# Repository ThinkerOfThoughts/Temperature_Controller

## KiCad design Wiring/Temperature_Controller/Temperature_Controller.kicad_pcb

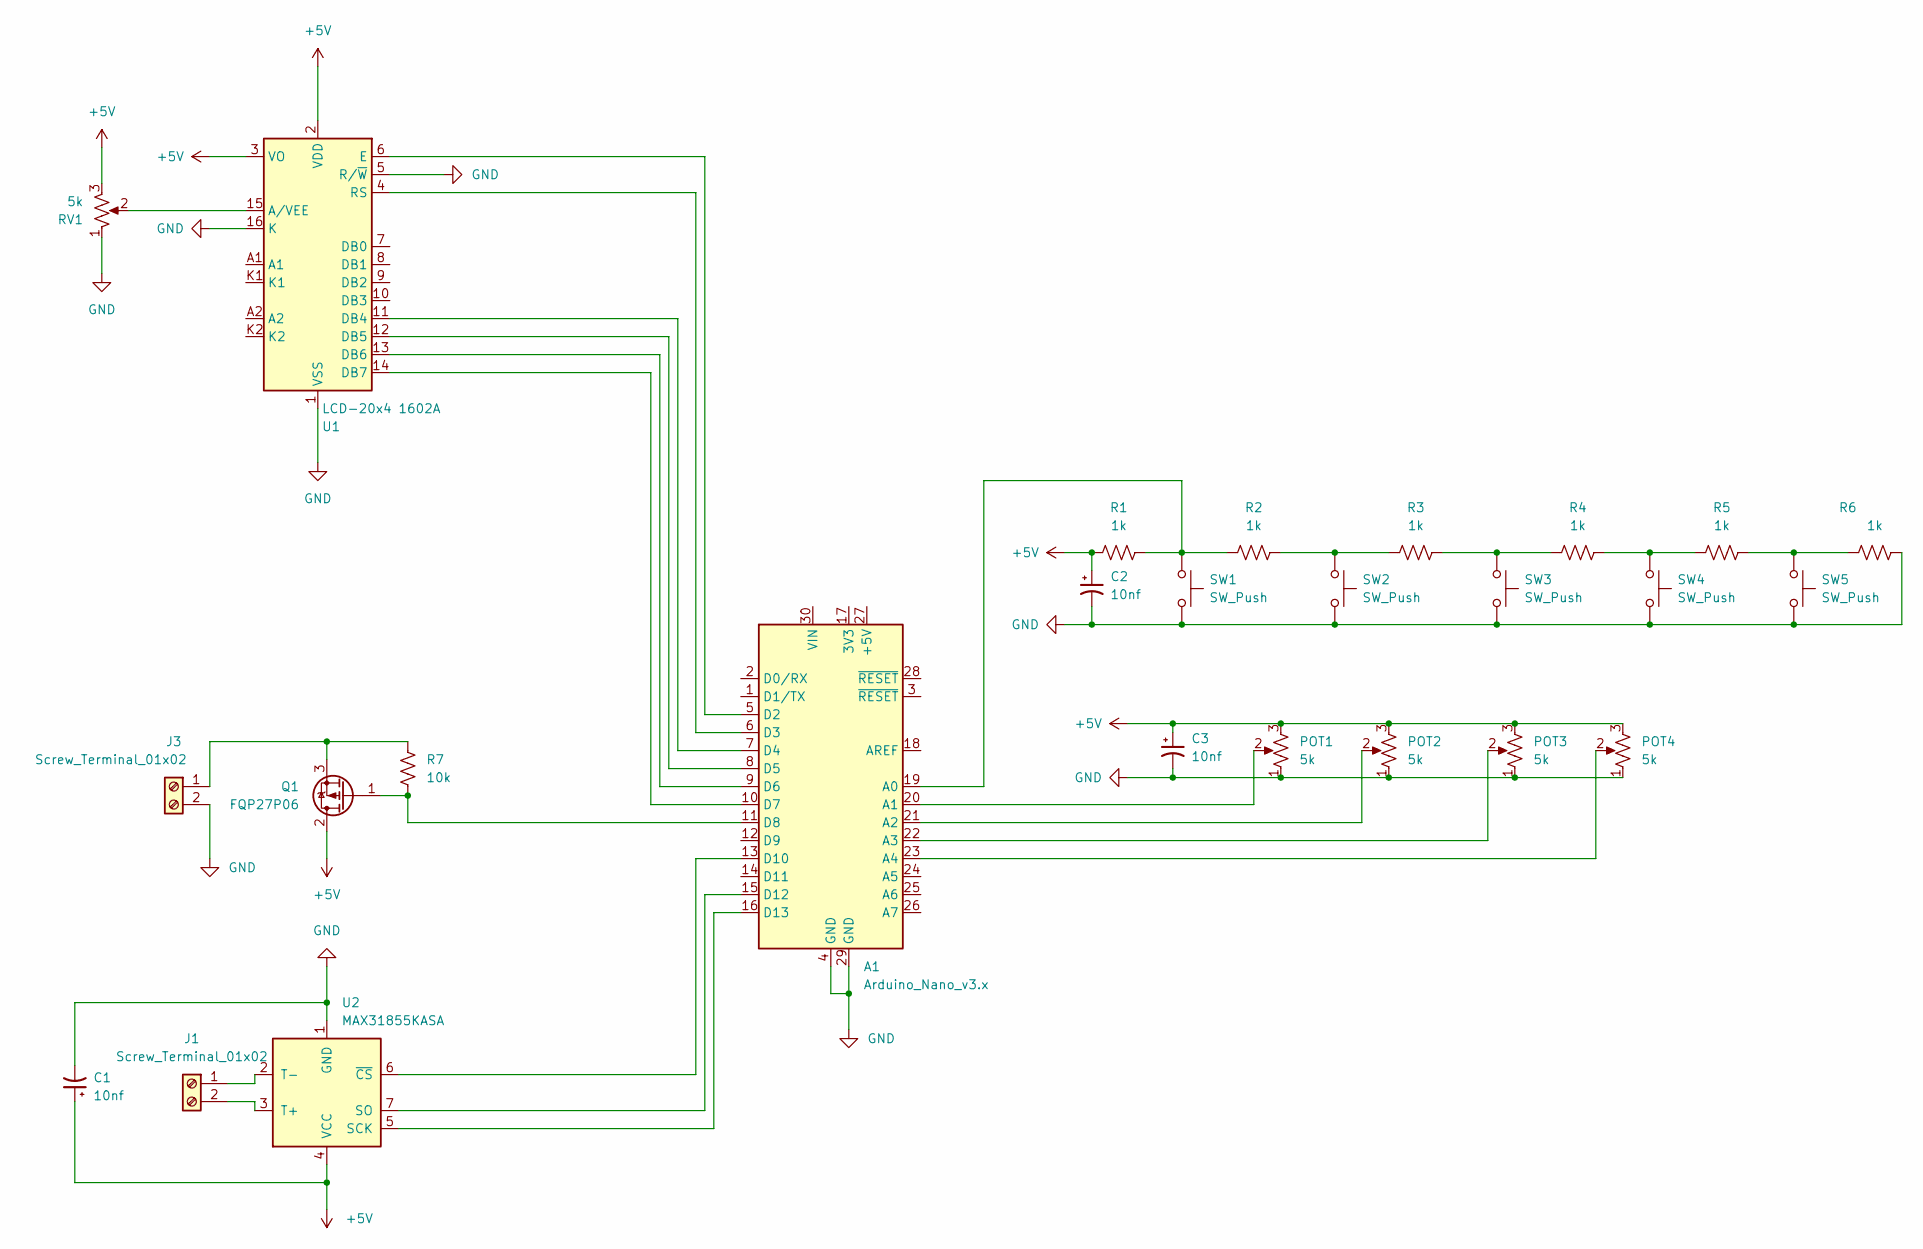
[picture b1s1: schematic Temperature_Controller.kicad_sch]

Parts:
A1: Arduino_Nano_v3.x; Arduino_Nano
C1, C2, C3: 10nf; CP_Radial_D12.5mm_P7.50mm
J1, J3: Screw_Terminal_01x02; TerminalBlock_Altech_AK300-2_P5.00mm
POT1, POT2, POT3, POT4: 5k; Potentiometer_Piher_T-16H_Single_Horizontal
Q1: FQP27P06; TO-220-3_Vertical
R1, R2, R3, R4, R5, R6: 1k; R_Axial_DIN0207_L6.3mm_D2.5mm_P10.16mm_Horizontal
R7: 10k; R_Axial_DIN0207_L6.3mm_D2.5mm_P10.16mm_Horizontal
RV1: 5k; Potentiometer_Piher_T-16H_Single_Horizontal
SW1, SW2, SW3, SW4, SW5: SW_Push; SW_PUSH_6mm
U1: LCD-20x4 1602A; LCD-016N002L
U2: MAX31855KASA; SOIC-8_3.9x4.9mm_P1.27mm

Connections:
+5V: C1.1, C2.1, C3.1, POT1.3, POT2.3, POT3.3, POT4.3, Q1.2 (D), R1.1, RV1.3, U1.2 (VDD), U1.3 (VO), U2.4 (VCC)
GND: A1.4 (GND), A1.29 (GND), C1.2, C2.2, C3.2, J3.2, POT1.1, POT2.1, POT3.1, POT4.1, R6.2, RV1.1, SW1.2, SW2.2, SW3.2, SW4.2, SW5.2, U1.1 (VSS), U1.5 (R/~W), U1.16 (K), U2.1 (GND)
unnamed: A1.5 (D2), U1.6 (E)
unnamed: A1.6 (D3), U1.4 (RS)
unnamed: A1.7 (D4), U1.11 (DB4)
unnamed: A1.8 (D5), U1.12 (DB5)
unnamed: A1.9 (D6), U1.13 (DB6)
unnamed: A1.10 (D7), U1.14 (DB7)
unnamed: A1.11 (D8), Q1.1 (G), R7.2
unnamed: A1.13 (D10), U2.6 (~CS)
unnamed: A1.15 (D12), U2.7 (SO)
unnamed: A1.16 (D13), U2.5 (SCK)
unnamed: A1.19 (A0), R1.2, R2.1, SW1.1
unnamed: A1.20 (A1), POT1.2
unnamed: A1.21 (A2), POT2.2
unnamed: A1.22 (A3), POT3.2
unnamed: A1.23 (A4), POT4.2
unnamed: J1.1, U2.2 (T-)
unnamed: J1.2, U2.3 (T+)
unnamed: J3.1, Q1.3 (S), R7.1
unnamed: R2.2, R3.1, SW2.1
unnamed: R3.2, R4.1, SW3.1
unnamed: R4.2, R5.1, SW4.1
unnamed: R5.2, R6.1, SW5.1
unnamed: RV1.2, U1.15 (A/VEE)

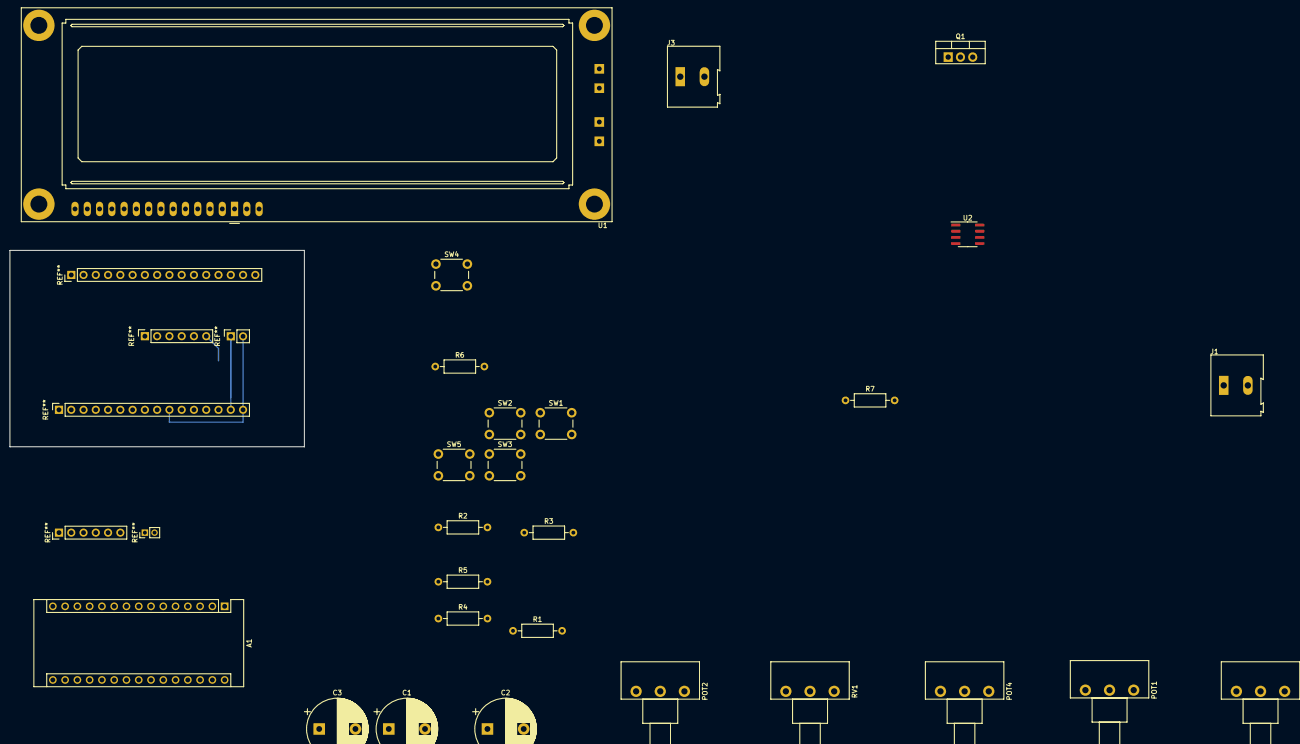
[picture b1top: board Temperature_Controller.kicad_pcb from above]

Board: 2 copper layers, 61.0 x 40.6 mm, 26 parts (0 on the bottom side), 25 nets.
